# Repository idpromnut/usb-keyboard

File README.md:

# USB Keyboard Firmware Project
This project started out as a STM32F103 firmware to convert the IBM Model M into a USB keyboard using the existing case, keys and membrane of the IBM Model-M 101 keyboard.

References:

- idollar for an excellent map of keys to the membrane in the Model-M keyboard (https://deskthority.net/workshop-f7/universal-model-m-controller-t9820.html#p207736)

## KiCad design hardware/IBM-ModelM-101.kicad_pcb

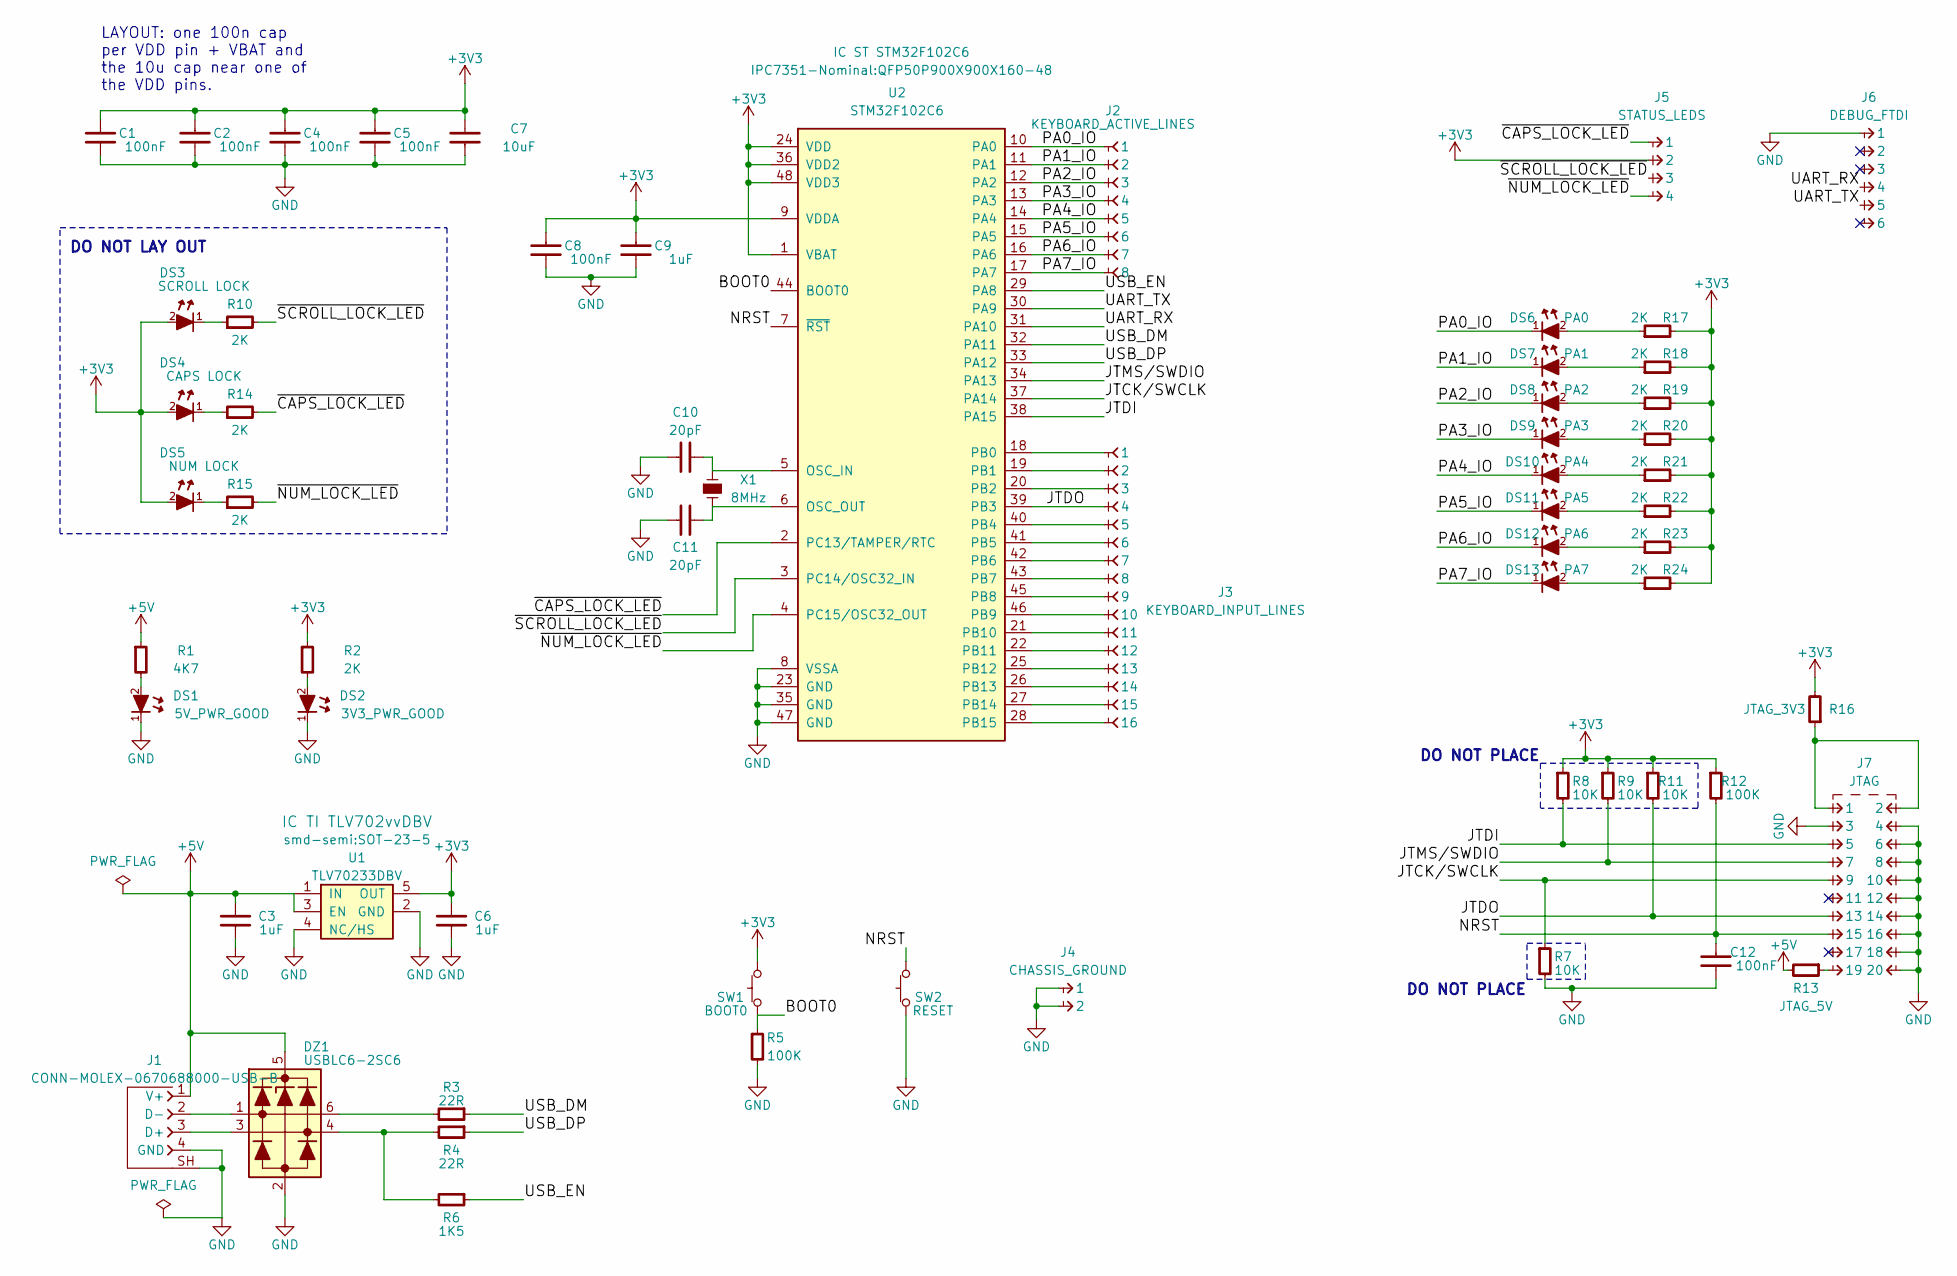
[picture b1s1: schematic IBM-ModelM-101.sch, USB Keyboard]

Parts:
C1, C2, C4, C5, C8, C12: 100nF; CAPC1608X55
C3, C6: 1uF; CAPC2012X70
C7: 10uF; CAPC2012X70
C9: 1uF; CAPC1608X55
C10, C11: 20pF; CAPC1608X55
DS1: 5V_PWR_GOOD; LED-0603
DS2: 3V3_PWR_GOOD; LED-0603
DS3: SCROLL LOCK; LED-0603
DS4: CAPS LOCK; LED-0603
DS5: NUM LOCK; LED-0603
DS6: PA0; LED-0603
DS7: PA1; LED-0603
DS8: PA2; LED-0603
DS9: PA3; LED-0603
DS10: PA4; LED-0603
DS11: PA5; LED-0603
DS12: PA6; LED-0603
DS13: PA7; LED-0603
DZ1: USBLC6-2SC6; SOT-23-6
J1: CONN-MOLEX-0670688000-USB-B; CONN-MOLEX-0670688000-USB_B
J2: KEYBOARD_ACTIVE_LINES; CONN-100MIL-F-1x8
J3: KEYBOARD_INPUT_LINES; CONN-100MIL-F-1x16
J4: CHASSIS_GROUND; CONN-MOLEX-0197134001-TAB
J5: STATUS_LEDS; CONN-100MIL-M-1x4-SHROUD
J6: DEBUG_FTDI; CONN-100MIL-M-1x6
J7: JTAG; CONN-100MIL-M-2x10-SHROUD
R1: 4K7; RESC1608X50
R2, R10, R14, R15, R17, R18, R19, R20, R21, R22, R23, R24: 2K; RESC1608X50
R3, R4: 22R; RESC1608X50
R5, R12: 100K; RESC1608X50
R6: 1K5; RESC1608X50
R7, R8, R9, R11: 10K; RESC1608X50
R13: JTAG_5V; RESC1608X50
R16: JTAG_3V3; RESC1608X50
SW1: BOOT0; TE-FSMSM
SW2: RESET; TE-FSMSM
U1: TLV70233DBV; SOT-23-5
U2: STM32F102C6; QFP50P900X900X160-48
X1: 8MHz; Abracon-ABM2

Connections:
+3V3: C1.2, C2.2, C4.2, C5.2, C6.1, C7.1, C8.2, C9.2, DS3.2 (A), DS4.2 (A), DS5.2 (A), J5.2, R2.1, R8.1, R9.1, R11.1, R12.1, R16.2, R17.2, R18.2, R19.2, R20.2, R21.2, R22.2, R23.2, R24.2, SW1.2, U1.5 (OUT), U2.1 (VBAT), U2.9 (VDDA), U2.24 (VDD), U2.36 (VDD2), U2.48 (VDD3)
+5V: C3.1, DZ1.5, J1.1 (V+), R1.1, R13.2, U1.1 (IN), U1.3 (EN)
/BOOT0: R5.1, SW1.1, U2.44 (BOOT0)
/JTCK/SWCLK: J7.9, R7.1, U2.37 (PA14)
/JTDI: J7.5, R8.2, U2.38 (PA15)
/JTDO: J3.4, J7.13, R11.2, U2.39 (PB3)
/JTMS/SWDIO: J7.7, R9.2, U2.34 (PA13)
/NRST: C12.2, J7.15, R12.2, SW2.2, U2.7 (~RST)
/PA0_IO: DS6.1 (K), J2.1, U2.10 (PA0)
/PA1_IO: DS7.1 (K), J2.2, U2.11 (PA1)
/PA2_IO: DS8.1 (K), J2.3, U2.12 (PA2)
/PA3_IO: DS9.1 (K), J2.4, U2.13 (PA3)
/PA4_IO: DS10.1 (K), J2.5, U2.14 (PA4)
/PA5_IO: DS11.1 (K), J2.6, U2.15 (PA5)
/PA6_IO: DS12.1 (K), J2.7, U2.16 (PA6)
/PA7_IO: DS13.1 (K), J2.8, U2.17 (PA7)
/UART_RX: J6.4, U2.31 (PA10)
/UART_TX: J6.5, U2.30 (PA9)
/USB_DM: R3.1, U2.32 (PA11)
/USB_DP: R4.1, U2.33 (PA12)
/USB_EN: R6.1, U2.29 (PA8)
/~CAPS_LOCK_LED~: J5.1, R14.2, U2.2 (PC13/TAMPER/RTC)
/~NUM_LOCK_LED~: J5.4, R15.2, U2.4 (PC15/OSC32_OUT)
/~SCROLL_LOCK_LED~: J5.3, R10.2, U2.3 (PC14/OSC32_IN)
GND: C1.1, C2.1, C3.2, C4.1, C5.1, C6.2, C7.2, C8.1, C9.1, C10.2, C11.2, C12.1, DS1.1 (K), DS2.1 (K), DZ1.2, J1.4 (GND), J1.SH (SHIELD), J4.1, J4.2, J6.1, J7.3, J7.4, J7.6, J7.8, J7.10, J7.12, J7.14, J7.16, J7.18, J7.20, R5.2, R7.2, SW2.1, U1.2 (GND), U1.4 (NC/HS), U2.8 (VSSA), U2.23 (GND), U2.35 (GND), U2.47 (GND)
unnamed: C10.1, U2.5 (OSC_IN), X1.1
unnamed: C11.1, U2.6 (OSC_OUT), X1.2
unnamed: DS1.2 (A), R1.2
unnamed: DS2.2 (A), R2.2
unnamed: DS3.1 (K), R10.1
unnamed: DS4.1 (K), R14.1
unnamed: DS5.1 (K), R15.1
unnamed: DS6.2 (A), R17.1
unnamed: DS7.2 (A), R18.1
unnamed: DS8.2 (A), R19.1
unnamed: DS9.2 (A), R20.1
unnamed: DS10.2 (A), R21.1
unnamed: DS11.2 (A), R22.1
unnamed: DS12.2 (A), R23.1
unnamed: DS13.2 (A), R24.1
unnamed: DZ1.1, J1.2 (D-)
unnamed: DZ1.3, J1.3 (D+)
unnamed: DZ1.4, R4.2, R6.2
unnamed: DZ1.6, R3.2
unnamed: J3.1, U2.18 (PB0)
unnamed: J3.2, U2.19 (PB1)
unnamed: J3.3, U2.20 (PB2)
unnamed: J3.5, U2.40 (PB4)
unnamed: J3.6, U2.41 (PB5)
unnamed: J3.7, U2.42 (PB6)
unnamed: J3.8, U2.43 (PB7)
unnamed: J3.9, U2.45 (PB8)
unnamed: J3.10, U2.46 (PB9)
unnamed: J3.11, U2.21 (PB10)
unnamed: J3.12, U2.22 (PB11)
unnamed: J3.13, U2.25 (PB12)
unnamed: J3.14, U2.26 (PB13)
unnamed: J3.15, U2.27 (PB14)
unnamed: J3.16, U2.28 (PB15)
unnamed: J7.1, J7.2, R16.1
unnamed: J7.19, R13.1

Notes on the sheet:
LAYOUT: one 100n cap per VDD pin + VBAT and the 10u cap near one of the VDD pins.
DO NOT PLACE
DO NOT LAY OUT

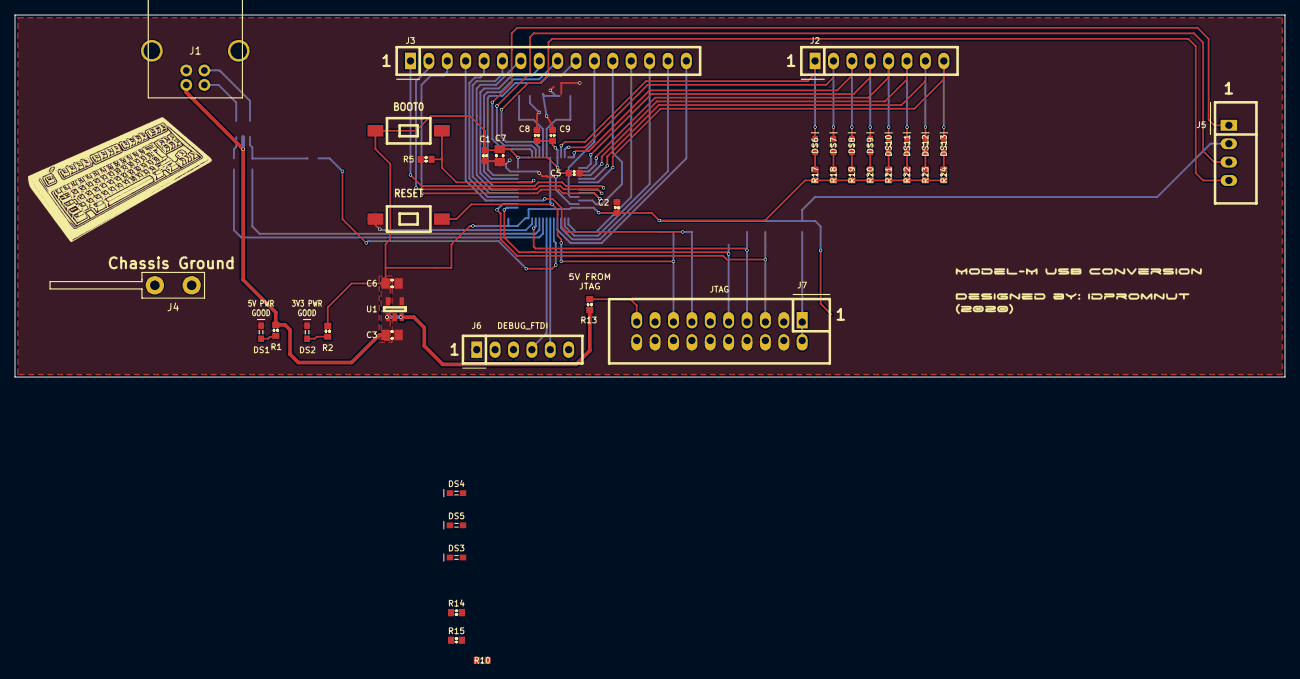
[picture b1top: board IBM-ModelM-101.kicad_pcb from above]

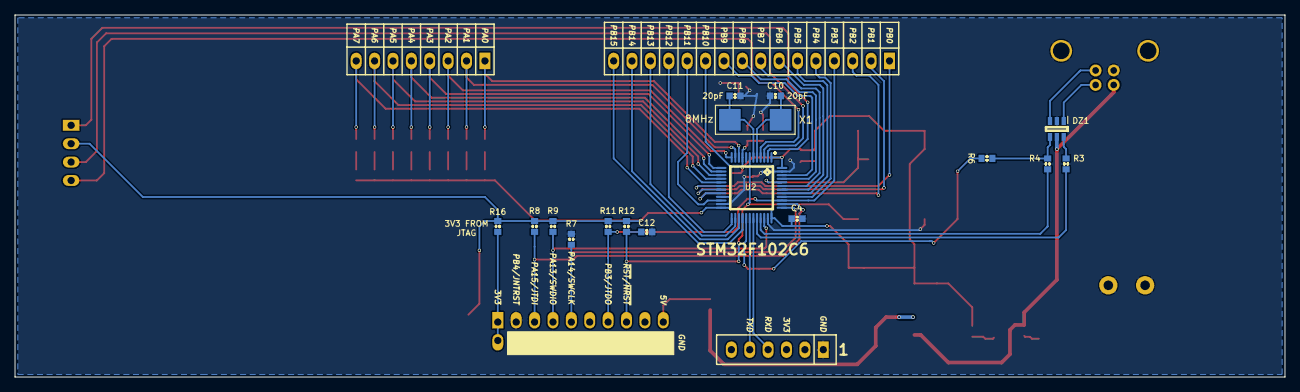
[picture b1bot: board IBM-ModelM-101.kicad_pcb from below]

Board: 2 copper layers, 175.4 x 50.0 mm, 62 parts (16 on the bottom side), 61 nets.

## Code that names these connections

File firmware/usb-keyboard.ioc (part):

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Mcu.Name=STM32F102C(4-6)Tx
Mcu.Package=LQFP48
Mcu.UserName=STM32F102C6Tx
PA0-WKUP.GPIOParameters=PinState,GPIO_Label
PA0-WKUP.GPIO_Label=PA0_IO
PA0-WKUP.PinState=GPIO_PIN_RESET
PA0-WKUP.Signal=GPIO_Output
PA1.GPIOParameters=GPIO_Label
PA1.GPIO_Label=PA1_IO
PA1.Signal=GPIO_Output
PA10.Mode=Asynchronous
PA10.Signal=USART1_RX
PA11.Mode=Device
PA11.Signal=USB_DM
PA12.Mode=Device
PA12.Signal=USB_DP
PA2.GPIOParameters=GPIO_Label
PA2.GPIO_Label=PA2_IO
PA2.Signal=GPIO_Output
PA3.GPIOParameters=GPIO_Label
PA3.GPIO_Label=PA3_IO
PA3.Signal=GPIO_Output
PA4.GPIOParameters=GPIO_Label
PA4.GPIO_Label=PA4_IO
PA4.Signal=GPIO_Output
PA5.GPIOParameters=GPIO_Label
PA5.GPIO_Label=PA5_IO
PA5.Signal=GPIO_Output
PA6.GPIOParameters=GPIO_Label
PA6.GPIO_Label=PA6_IO
PA6.Signal=GPIO_Output
PA7.GPIOParameters=GPIO_Label
PA7.GPIO_Label=PA7_IO
PA7.Signal=GPIO_Output
PA8.GPIOParameters=GPIO_Label
PA8.GPIO_Label=USB_EN
PA8.Signal=GPIO_Output
PA9.Mode=Asynchronous
PA9.Signal=USART1_TX
PB0.GPIOParameters=GPIO_Label
PB0.GPIO_Label=PB0_INPUT
PB0.Signal=GPIO_Input
PB1.GPIOParameters=GPIO_Label
PB1.GPIO_Label=PB1_INPUT
PB1.Signal=GPIO_Input
PB10.GPIOParameters=GPIO_Label
PB10.GPIO_Label=PB10_INPUT
PB10.Signal=GPIO_Input
PB11.GPIOParameters=GPIO_Label
PB11.GPIO_Label=PB11_INPUT
PB11.Signal=GPIO_Input
PB12.GPIOParameters=GPIO_Label
PB12.GPIO_Label=PB12_INPUT
PB12.Signal=GPIO_Input
PB13.GPIOParameters=GPIO_Label
PB13.GPIO_Label=PB13_INPUT
PB13.Signal=GPIO_Input
PB14.GPIOParameters=GPIO_Label
PB14.GPIO_Label=PB14_INPUT
PB14.Signal=GPIO_Input
PB15.GPIOParameters=GPIO_Label
PB15.GPIO_Label=PB15_INPUT
PB15.Signal=GPIO_Input
PB2.GPIOParameters=GPIO_Label
PB2.GPIO_Label=PB2_INPUT
PB2.Signal=GPIO_Input
PB3.GPIOParameters=GPIO_Label
PB3.GPIO_Label=PB3_INPUT
PB3.Signal=GPIO_Input
PB4.GPIOParameters=GPIO_Label
PB4.GPIO_Label=PB4_INPUT
PB4.Signal=GPIO_Input
PB5.GPIOParameters=GPIO_Label
PB5.GPIO_Label=PB5_INPUT
PB5.Signal=GPIO_Input
PB6.GPIOParameters=GPIO_Label
PB6.GPIO_Label=PB6_INPUT
PB6.Signal=GPIO_Input
PB7.GPIOParameters=GPIO_Label
PB7.GPIO_Label=PB7_INPUT
PB7.Signal=GPIO_Input
PB8.GPIOParameters=GPIO_Label
PB8.GPIO_Label=PB8_INPUT
PB8.Signal=GPIO_Input
PB9.GPIOParameters=GPIO_Label
PB9.GPIO_Label=PB9_INPUT
PB9.Signal=GPIO_Input
PC13-TAMPER-RTC.GPIOParameters=PinState,GPIO_Label,GPIO_ModeDefaultOutputPP
PC13-TAMPER-RTC.GPIO_Label=CAPS_LOCK_LED
PC13-TAMPER-RTC.GPIO_ModeDefaultOutputPP=GPIO_MODE_OUTPUT_OD
PC13-TAMPER-RTC.PinState=GPIO_PIN_SET
PC13-TAMPER-RTC.Signal=GPIO_Output
PC14-OSC32_IN.GPIOParameters=PinState,GPIO_Label,GPIO_ModeDefaultOutputPP
PC14-OSC32_IN.GPIO_Label=SCROLL_LOCK_LED
PC14-OSC32_IN.GPIO_ModeDefaultOutputPP=GPIO_MODE_OUTPUT_OD
PC14-OSC32_IN.PinState=GPIO_PIN_SET
PC14-OSC32_IN.Signal=GPIO_Output
PC15-OSC32_OUT.GPIOParameters=PinState,GPIO_Label,GPIO_ModeDefaultOutputPP
PC15-OSC32_OUT.GPIO_Label=NUM_LOCK_LED
PC15-OSC32_OUT.GPIO_ModeDefaultOutputPP=GPIO_MODE_OUTPUT_OD
PC15-OSC32_OUT.PinState=GPIO_PIN_SET
PC15-OSC32_OUT.Signal=GPIO_Output
PD0-OSC_IN.Mode=HSE-External-Oscillator
PD0-OSC_IN.Signal=RCC_OSC_IN
PD1-OSC_OUT.Mode=HSE-External-Oscillator
PD1-OSC_OUT.Signal=RCC_OSC_OUT
RCC.SYSCLKFreq_VALUE=48000000
RCC.SYSCLKSource=RCC_SYSCLKSOURCE_PLLCLK
board=custom

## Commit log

2016-05-13 Check in of basic CDC-based STM32F103 project
2016-05-13 Renamed project to Model-M
    Also enabled CDC USB init in main, that was commented out for testing
    the SemiHosting debug printf().
2016-05-13 Fixed naming
2016-05-14 Project file updates
2016-05-15 Got key scanning code working
    Scanning is done 16bits at a time over 8 output lines.
2016-05-15 Rename to "generic" keyboard firmware
    Looks like this can be somewhat generic so I'll rename and re-organize
    the firmware to be usable for other keyboards.
2016-05-16 Refactoring and debugging
2016-05-17 Started work on Keymap
    Worked on mapping key position in IBM Model-M keyboard to USB scan
    codes.
2016-05-17 Removed build files.
2016-05-18 Reorganized firmware
    Moved the firmware into its own directory and created a directory for
    the hardware files.
2016-05-18 Added beginning of schematic for USB replacement PCB
    Schematic and PCB files + documentation for uC.
2016-05-19 Completed most of the keyboard circuit
    Missing the LED connector, decoupling caps, a power LED of some sort,
    and the ground spade connector.
2016-05-19 Finished power and boot/reset circuits
2016-05-23 Finished schematic, started work on PCB layout
2016-05-24 Working on PCB layout
    Placement is done. Most of the power, decoupling and support routing
    finished.
2016-05-25 Laying out PCB
2016-05-25 Re-working crystal selection and routing.
2016-06-06 Finished PCB layout
2016-06-07 Updates + replaced tab header with correct footprint
2016-06-09 Fixed unconnected pads + ground plane.
2016-06-10 Added artwork and logo
2016-06-16 Added keyboard art
    Source files used to generate silk screen art for the Model-M PCB.
2016-06-19 Final fixes to schematic and PCB layout
    Fixed silk screen errors, added pin-out information to I/O headers and
    JTAG.
2016-06-19 Adjusted output gerber naming
2016-07-23 Converting to STM32F102
2016-07-26 Updates to support the STM32F102
    Added STM32F102x6 startup file.
2016-08-14 Most keys, locks working
    All alpha-numerics working along with Scroll, Num andCaps lock keys.
    Shift, Alt and Ctrl not working. Enter key seems to have a bug with it
    as well.
2016-08-15 Fixed Enter key
2016-09-01 Set report response not working
    Set Report received, but no response is sent.
2016-09-13 Set Report working
    Still need to hook up the set report messages to the LED control code.
2016-09-15 Leds are now working
2016-09-26 Fixed incorrect HID_EPIN_SIZE
    Fixed a typo that prevented the HID keyboard from working.
2017-07-08 Fixed key repeat code
    Keys will now stop repeating if a modifier key is released or pressed.
    Key repeat will pause 500msec before turning on.
2018-04-21 Moved debug UART configuration to main.h
2018-04-21 Refactored directory structure
    Put BSP-related code into src, Drivers and Middleware. BSP-related code is now in src/bsp.
2020-07-13 Updated schematic and PCB layout to fix errors in first revision.
2020-07-13 Updated usb-keyboard firmware to use STM's STM32CubeIDE.
2020-07-13 Updated copyright information.
